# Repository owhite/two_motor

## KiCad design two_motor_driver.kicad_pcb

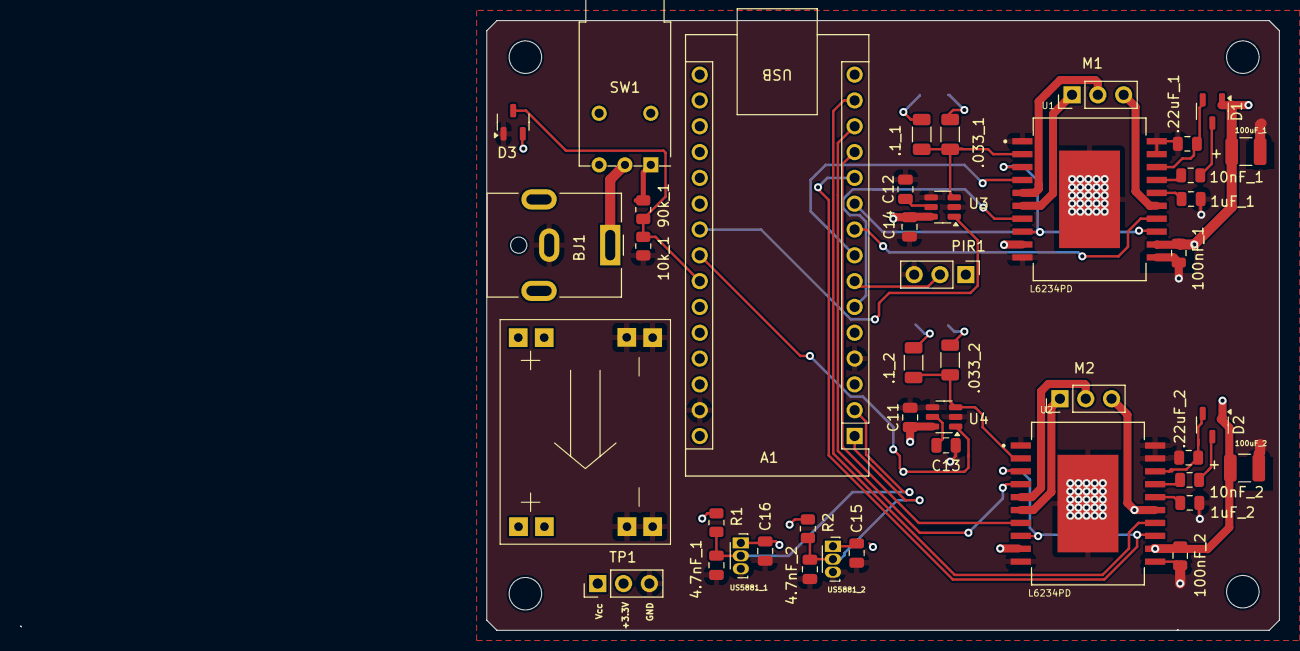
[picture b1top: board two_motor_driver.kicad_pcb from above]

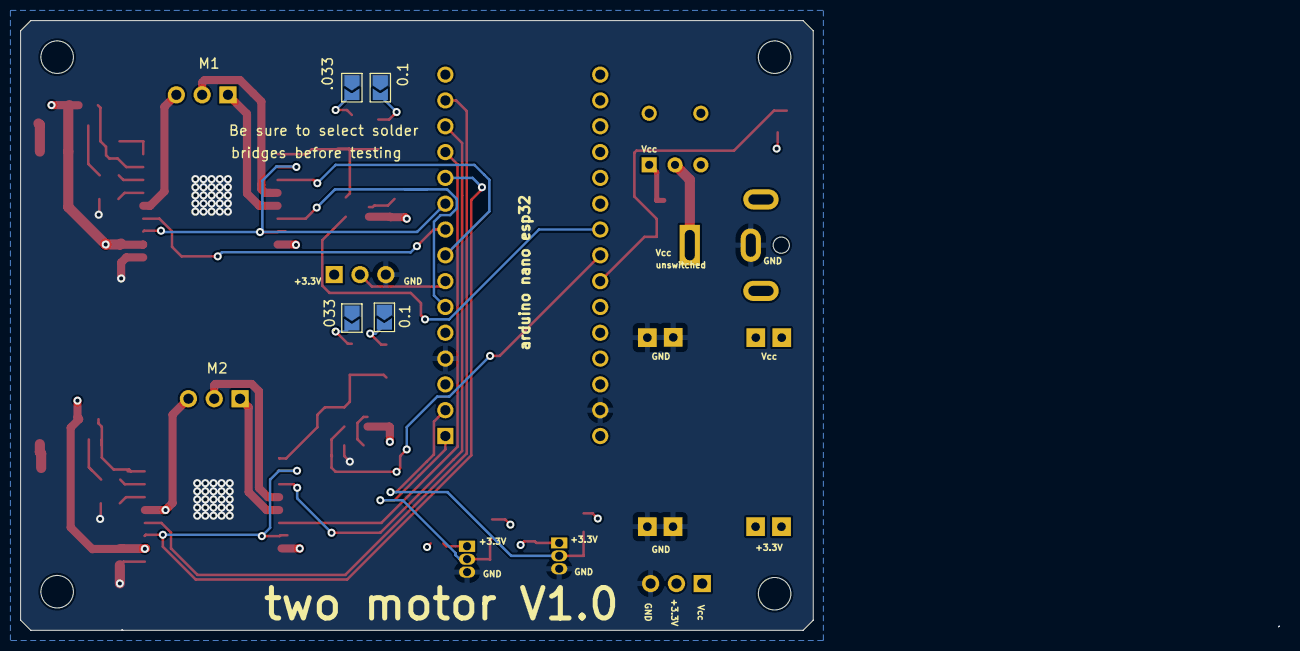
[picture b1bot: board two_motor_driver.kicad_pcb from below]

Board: 4 copper layers, 123.8 x 60.0 mm, 47 parts (4 on the bottom side), 40 nets.

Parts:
1uF_1, 1uF_2: 1uF; C_0805_2012Metric
4.7nF_1, 4.7nF_2: 4.7nF; C_0805_2012Metric
10k_1: 10k; R_0805_2012Metric
10nF_1, 10nF_2: 10nF; C_0805_2012Metric
90k_1: 90k; R_0805_2012Metric
100nF_1, 100nF_2: 100nF; C_0805_2012Metric
100uF_1, 100uF_2: 100uF; C_1210_3225Metric
.1_1, .1_2: .1; R_1206_3216Metric
.22uF_1, .22uF_2: .22uF; C_0805_2012Metric
.033_1, .033_2: .033; R_1206_3216Metric
A1: Arduino_Nano_ESP32; Arduino_Nano
BJ1: Barrel_Jack; BarrelJack_CUI_PJ-063AH_Horizontal
C11, C12, C13, C14, C15, C16: 100nF; C_0805_2012Metric
D1, D2, D3: BAT54S; SOT-23-3
JP1, JP3, JP4, JP5: SolderJumper_2_Open; SolderJumper-2_P1.3mm_Open_TrianglePad1.0x1.5mm
M1, M2: Conn_01x03; PinHeader_1x03_P2.54mm_Vertical
PIR1: Conn_01x03; PinHeader_1x03_P2.54mm_Vertical
R1, R2: 10k; R_0805_2012Metric
SW1: SW_SPDT; SW_NKK_BB15AH
TP1: Conn_01x03; PinHeader_1x03_P2.54mm_Vertical
U1, U2: L6234PD; SOIC127P1420X360-21N
U3, U4: INA181; SOT-23-6
U5: my_buck_boost
US5881_1, US5881_2: hall_effect_three_wire; Diodes_SIP-3_4.1x1.5mm_P1.27mm

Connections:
+3.3V: A1.17 (3V3), C11.1, C14.1, C15.1, C16.1, D3.2, PIR1.1, R1.1, R2.1, TP1.2, U3.6 (V+), U4.6 (V+), U5.7 (Reg_out), U5.8 (Reg_out), US5881_1.1 (V+), US5881_2.1 (V+)
GND: 1uF_1.2, 1uF_2.2, 4.7nF_1.2, 4.7nF_2.2, 10k_1.2, 100nF_1.2, 100nF_2.2, 100uF_1.2, 100uF_2.2, .22uF_1.2, .22uF_2.2, A1.4 (GND), A1.29 (GND), BJ1.2, C11.2, C12.2, C13.2, C14.2, C15.2, C16.2, D3.1, JP1.1 (A), JP3.1 (A), JP4.1 (A), JP5.1, PIR1.3, TP1.3, U1.1 (GND), U1.10 (GND), U1.11 (GND), U1.19 (SENSE2), U1.20 (GND), U1.21 (EP), U2.1 (GND), U2.10 (GND), U2.11 (GND), U2.19 (SENSE2), U2.20 (GND), U2.21 (EP), U3.2 (GND), U3.4 (-), U4.2 (GND), U4.4 (-), U5.1 (IN_-), U5.2 (IN_-), U5.5 (Reg_GND), U5.6 (Reg_GND), US5881_1.3 (V-), US5881_2.3 (V-)
HS1: 4.7nF_1.1, A1.2 (D0/RX), R1.2, US5881_1.2 (out)
HS2: 4.7nF_2.1, A1.1 (D1/TX), R2.2, US5881_2.2 (out)
M1_EN: A1.10 (D7), U1.3 (EN2), U1.8 (EN1), U1.13 (EN3)
M1_IN1: A1.6 (D3), U1.7 (IN1)
M1_IN2: A1.8 (D5), U1.4 (IN2)
M1_IN3: A1.9 (D6), U1.14 (IN3)
M2_EN: A1.11 (D8), U2.3 (EN2), U2.8 (EN1), U2.13 (EN3)
M2_IN1: A1.12 (D9), U2.7 (IN1)
M2_IN2: A1.13 (D10/CS), U2.4 (IN2)
M2_IN3: A1.14 (D11/COPI), U2.14 (IN3)
unnamed: 10nF_1.1, D1.3
unnamed: 10nF_2.1, D2.3
unnamed: .033_1.2, JP5.2
unnamed: .1_1.2, JP1.2 (B)
unnamed: .033_2.2, JP3.2 (B)
unnamed: .1_2.2, JP4.2 (B)
unnamed: BJ1.1, SW1.2 (B)
unnamed: C12.1, U3.5 (REF)
unnamed: C13.1, U4.5 (REF)
PIR: A1.7 (D4), PIR1.2
SENSE1_1: .1_1.1, .033_1.1, U1.2 (SENSE1), U3.3 (+)
SENSE1_1_out: A1.22 (A3), U3.1
SENSE1_2: .1_2.1, .033_2.1, U2.2 (SENSE1), U4.3 (+)
SENSE1_2_out: A1.23 (SDA/A4), U4.1
U1: M1.1, U1.6 (OUT1)
U2: M2.1, U2.6 (OUT1)
V1: M1.2, U1.5 (OUT2)
V2: M2.2, U2.5 (OUT2)
VBOOT1: .22uF_1.1, D1.2, U1.18 (VBOOT)
VBOOT2: .22uF_2.1, D2.2, U2.18 (VBOOT)
VCP1: 10nF_1.2, U1.17 (VCP)
VCP2: 10nF_2.2, U2.17 (VCP)
VREF1: 1uF_1.1, U1.16 (VREF)
VREF2: 1uF_2.1, U2.16 (VREF)
Vcc: 90k_1.1, 100nF_1.1, 100nF_2.1, 100uF_1.1, 100uF_2.1, D1.1, D2.1, SW1.1 (A), TP1.1, U1.9 (VS), U1.12 (VS), U2.9 (VS), U2.12 (VS), U5.3 (IN_+), U5.4 (IN_+)
Vcc_sense: 10k_1.1, 90k_1.2, A1.24 (SCL/A5), D3.3
W1: M1.3, U1.15 (OUT3)
W2: M2.3, U2.15 (OUT3)

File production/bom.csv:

Designator,Footprint,Quantity,Value,LCSC Part #
".033_1, .033_2",1206,2,.033,
".1_1, .1_2",1206,2,.1,
".22UF_1, .22UF_2",0805,2,.22uF,
"100NF_1, 100NF_2, C11, C12, C13, C14, C15, C16",0805,8,100nF,
"100UF_1, 100UF_2",1210,2,100uF,
"10K_1, R1, R2",0805,3,10k,
"10NF_1, 10NF_2",0805,2,10nF,
"1UF_1, 1UF_2",0805,2,1uF,
"4.7NF_1, 4.7NF_2",0805,2,4.7nF,
90K_1,0805,1,90k,
A1,Arduino_Nano,1,Arduino_Nano_ESP32,
BJ1,BarrelJack_CUI_PJ-063AH_Horizontal,1,Barrel_Jack,
"D1, D2, D3",SOT-23-3,3,BAT54S,
"M1, M2, PIR1, TP1",PinHeader_1x03_P2.54mm_Vertical,4,Conn_01x03,
SW1,SW_NKK_BB15AH,1,SW_SPDT,
"U1, U2",SOIC127P1420X360-21N,2,L6234PD,
"U3, U4",SOT-23-6,2,INA181,
U5,my_buck_boost,1,my_buck_boost,
"US5881_1, US5881_2",Diodes_SIP-3_4.1x1.5mm_P1.27mm,2,hall_effect_three_wire,

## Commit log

2025-07-15 created firmware directory
2025-07-15 attempted nano programming
